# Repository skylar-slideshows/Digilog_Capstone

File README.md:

# Digitally Controlled Analog Mixing Console

### Capstone, 2026, Northeastern University Department of Electrical Engineering

### Contributors: Skylar Denno, Darya Petrova, Evan Forcucci, Xinhao Chen, Luke Garrity, Daniel Salas

### Advisor: [Milad Siami](https://coe.northeastern.edu/people/siami-milad/)

## [Firmware Documentation](https://docs.skylar.lgbt/)

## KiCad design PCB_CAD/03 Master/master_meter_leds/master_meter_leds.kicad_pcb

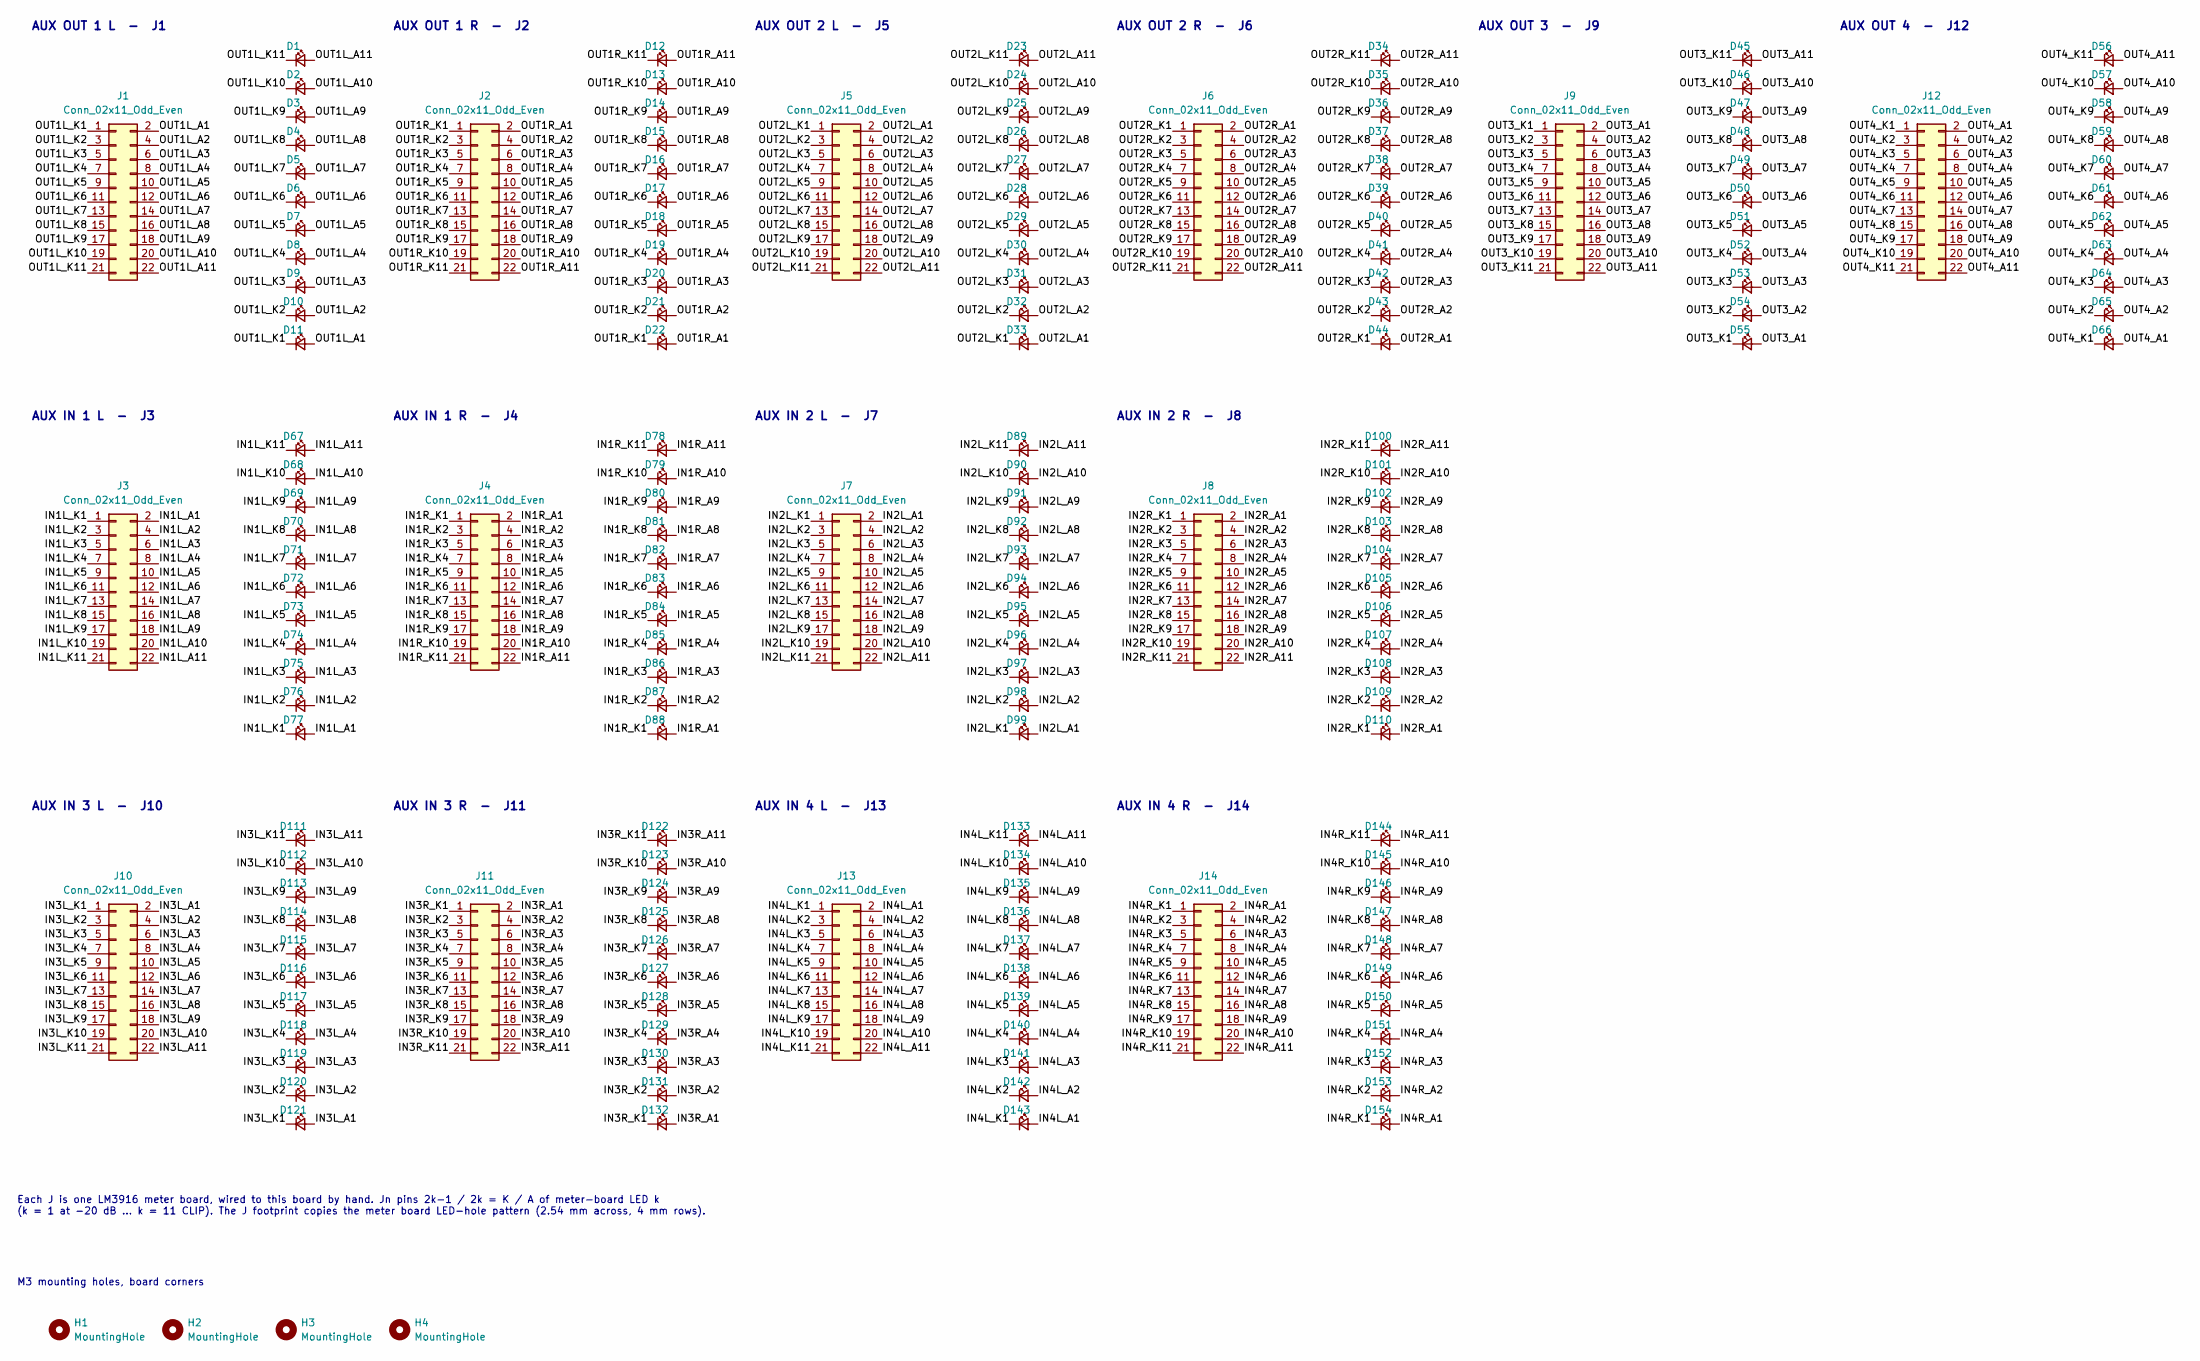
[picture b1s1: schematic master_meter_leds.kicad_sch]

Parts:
D1, D2, D3, D4, D5, D6, D7, D8, D9, D10, D11, D12, D13, D14, D15, D16, D17, D18, D19, D20, D21, D22, D23, D24, D25, D26, D27, D28, D29, D30, D31, D32, D33, D34, D35, D36, D37, D38, D39, D40, D41, D42, D43, D44, D45, D46, D47, D48, D49, D50, D51, D52, D53, D54, D55, D56, D57, D58, D59, D60, D61, D62, D63, D64, D65, D66, D67, D68, D69, D70, D71, D72, D73, D74, D75, D76, D77, D78, D79, D80, D81, D82, D83, D84, D85, D86, D87, D88, D89, D90, D91, D92, D93, D94, D95, D96, D97, D98, D99, D100, D101, D102, D103, D104, D105, D106, D107, D108, D109, D110, D111, D112, D113, D114, D115, D116, D117, D118, D119, D120, D121, D122, D123, D124, D125, D126, D127, D128, D129, D130, D131, D132, D133, D134, D135, D136, D137, D138, D139, D140, D141, D142, D143, D144, D145, D146, D147, D148, D149, D150, D151, D152, D153, D154: LED_Small; LED_Rectangular_W5.0mm_H2.0mm
H1, H2, H3, H4: MountingHole; MountingHole_3.2mm_M3
J1, J2, J3, J4, J5, J6, J7, J8, J9, J10, J11, J12, J13, J14: Conn_02x11_Odd_Even; LED_Meter_Wiring_11x2

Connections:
/IN1L_A1: D77.2 (A), J3.2
/IN1L_A2: D76.2 (A), J3.4
/IN1L_A3: D75.2 (A), J3.6
/IN1L_A4: D74.2 (A), J3.8
/IN1L_A5: D73.2 (A), J3.10
/IN1L_A6: D72.2 (A), J3.12
/IN1L_A7: D71.2 (A), J3.14
/IN1L_A8: D70.2 (A), J3.16
/IN1L_A9: D69.2 (A), J3.18
/IN1L_A10: D68.2 (A), J3.20
/IN1L_A11: D67.2 (A), J3.22
/IN1L_K1: D77.1 (K), J3.1
/IN1L_K2: D76.1 (K), J3.3
/IN1L_K3: D75.1 (K), J3.5
/IN1L_K4: D74.1 (K), J3.7
/IN1L_K5: D73.1 (K), J3.9
/IN1L_K6: D72.1 (K), J3.11
/IN1L_K7: D71.1 (K), J3.13
/IN1L_K8: D70.1 (K), J3.15
/IN1L_K9: D69.1 (K), J3.17
/IN1L_K10: D68.1 (K), J3.19
/IN1L_K11: D67.1 (K), J3.21
/IN1R_A1: D88.2 (A), J4.2
/IN1R_A2: D87.2 (A), J4.4
/IN1R_A3: D86.2 (A), J4.6
/IN1R_A4: D85.2 (A), J4.8
/IN1R_A5: D84.2 (A), J4.10
/IN1R_A6: D83.2 (A), J4.12
/IN1R_A7: D82.2 (A), J4.14
/IN1R_A8: D81.2 (A), J4.16
/IN1R_A9: D80.2 (A), J4.18
/IN1R_A10: D79.2 (A), J4.20
/IN1R_A11: D78.2 (A), J4.22
/IN1R_K1: D88.1 (K), J4.1
/IN1R_K2: D87.1 (K), J4.3
/IN1R_K3: D86.1 (K), J4.5
/IN1R_K4: D85.1 (K), J4.7
/IN1R_K5: D84.1 (K), J4.9
/IN1R_K6: D83.1 (K), J4.11
/IN1R_K7: D82.1 (K), J4.13
/IN1R_K8: D81.1 (K), J4.15
/IN1R_K9: D80.1 (K), J4.17
/IN1R_K10: D79.1 (K), J4.19
/IN1R_K11: D78.1 (K), J4.21
/IN2L_A1: D99.2 (A), J7.2
/IN2L_A2: D98.2 (A), J7.4
/IN2L_A3: D97.2 (A), J7.6
/IN2L_A4: D96.2 (A), J7.8
/IN2L_A5: D95.2 (A), J7.10
/IN2L_A6: D94.2 (A), J7.12
/IN2L_A7: D93.2 (A), J7.14
/IN2L_A8: D92.2 (A), J7.16
/IN2L_A9: D91.2 (A), J7.18
/IN2L_A10: D90.2 (A), J7.20
/IN2L_A11: D89.2 (A), J7.22
/IN2L_K1: D99.1 (K), J7.1
/IN2L_K2: D98.1 (K), J7.3
/IN2L_K3: D97.1 (K), J7.5
/IN2L_K4: D96.1 (K), J7.7
/IN2L_K5: D95.1 (K), J7.9
/IN2L_K6: D94.1 (K), J7.11
/IN2L_K7: D93.1 (K), J7.13
/IN2L_K8: D92.1 (K), J7.15
/IN2L_K9: D91.1 (K), J7.17
/IN2L_K10: D90.1 (K), J7.19
/IN2L_K11: D89.1 (K), J7.21
/IN2R_A1: D110.2 (A), J8.2
/IN2R_A2: D109.2 (A), J8.4
/IN2R_A3: D108.2 (A), J8.6
/IN2R_A4: D107.2 (A), J8.8
/IN2R_A5: D106.2 (A), J8.10
/IN2R_A6: D105.2 (A), J8.12
/IN2R_A7: D104.2 (A), J8.14
/IN2R_A8: D103.2 (A), J8.16
/IN2R_A9: D102.2 (A), J8.18
/IN2R_A10: D101.2 (A), J8.20
/IN2R_A11: D100.2 (A), J8.22
/IN2R_K1: D110.1 (K), J8.1
/IN2R_K2: D109.1 (K), J8.3
/IN2R_K3: D108.1 (K), J8.5
/IN2R_K4: D107.1 (K), J8.7
/IN2R_K5: D106.1 (K), J8.9
/IN2R_K6: D105.1 (K), J8.11
/IN2R_K7: D104.1 (K), J8.13
/IN2R_K8: D103.1 (K), J8.15
/IN2R_K9: D102.1 (K), J8.17
/IN2R_K10: D101.1 (K), J8.19
/IN2R_K11: D100.1 (K), J8.21
/IN3L_A1: D121.2 (A), J10.2
/IN3L_A2: D120.2 (A), J10.4
/IN3L_A3: D119.2 (A), J10.6
/IN3L_A4: D118.2 (A), J10.8
/IN3L_A5: D117.2 (A), J10.10
/IN3L_A6: D116.2 (A), J10.12
/IN3L_A7: D115.2 (A), J10.14
/IN3L_A8: D114.2 (A), J10.16
/IN3L_A9: D113.2 (A), J10.18
/IN3L_A10: D112.2 (A), J10.20
/IN3L_A11: D111.2 (A), J10.22
/IN3L_K1: D121.1 (K), J10.1
/IN3L_K2: D120.1 (K), J10.3
/IN3L_K3: D119.1 (K), J10.5
/IN3L_K4: D118.1 (K), J10.7
/IN3L_K5: D117.1 (K), J10.9
/IN3L_K6: D116.1 (K), J10.11
/IN3L_K7: D115.1 (K), J10.13
/IN3L_K8: D114.1 (K), J10.15
/IN3L_K9: D113.1 (K), J10.17
/IN3L_K10: D112.1 (K), J10.19
/IN3L_K11: D111.1 (K), J10.21
/IN3R_A1: D132.2 (A), J11.2
/IN3R_A2: D131.2 (A), J11.4
/IN3R_A3: D130.2 (A), J11.6
/IN3R_A4: D129.2 (A), J11.8
/IN3R_A5: D128.2 (A), J11.10
/IN3R_A6: D127.2 (A), J11.12
/IN3R_A7: D126.2 (A), J11.14
/IN3R_A8: D125.2 (A), J11.16
/IN3R_A9: D124.2 (A), J11.18
/IN3R_A10: D123.2 (A), J11.20
/IN3R_A11: D122.2 (A), J11.22
/IN3R_K1: D132.1 (K), J11.1
/IN3R_K2: D131.1 (K), J11.3
/IN3R_K3: D130.1 (K), J11.5
/IN3R_K4: D129.1 (K), J11.7
/IN3R_K5: D128.1 (K), J11.9
/IN3R_K6: D127.1 (K), J11.11
/IN3R_K7: D126.1 (K), J11.13
/IN3R_K8: D125.1 (K), J11.15
/IN3R_K9: D124.1 (K), J11.17
/IN3R_K10: D123.1 (K), J11.19
/IN3R_K11: D122.1 (K), J11.21
/IN4L_A1: D143.2 (A), J13.2
/IN4L_A2: D142.2 (A), J13.4
/IN4L_A3: D141.2 (A), J13.6
/IN4L_A4: D140.2 (A), J13.8
/IN4L_A5: D139.2 (A), J13.10
/IN4L_A6: D138.2 (A), J13.12
/IN4L_A7: D137.2 (A), J13.14
/IN4L_A8: D136.2 (A), J13.16
/IN4L_A9: D135.2 (A), J13.18
/IN4L_A10: D134.2 (A), J13.20
/IN4L_A11: D133.2 (A), J13.22
/IN4L_K1: D143.1 (K), J13.1
/IN4L_K2: D142.1 (K), J13.3
/IN4L_K3: D141.1 (K), J13.5
/IN4L_K4: D140.1 (K), J13.7
/IN4L_K5: D139.1 (K), J13.9
/IN4L_K6: D138.1 (K), J13.11
/IN4L_K7: D137.1 (K), J13.13
/IN4L_K8: D136.1 (K), J13.15
/IN4L_K9: D135.1 (K), J13.17
/IN4L_K10: D134.1 (K), J13.19
/IN4L_K11: D133.1 (K), J13.21
/IN4R_A1: D154.2 (A), J14.2
/IN4R_A2: D153.2 (A), J14.4
/IN4R_A3: D152.2 (A), J14.6
/IN4R_A4: D151.2 (A), J14.8
/IN4R_A5: D150.2 (A), J14.10
/IN4R_A6: D149.2 (A), J14.12
/IN4R_A7: D148.2 (A), J14.14
/IN4R_A8: D147.2 (A), J14.16
/IN4R_A9: D146.2 (A), J14.18
/IN4R_A10: D145.2 (A), J14.20
/IN4R_A11: D144.2 (A), J14.22
/IN4R_K1: D154.1 (K), J14.1
/IN4R_K2: D153.1 (K), J14.3
/IN4R_K3: D152.1 (K), J14.5
/IN4R_K4: D151.1 (K), J14.7
/IN4R_K5: D150.1 (K), J14.9
/IN4R_K6: D149.1 (K), J14.11
/IN4R_K7: D148.1 (K), J14.13
/IN4R_K8: D147.1 (K), J14.15
/IN4R_K9: D146.1 (K), J14.17
/IN4R_K10: D145.1 (K), J14.19
/IN4R_K11: D144.1 (K), J14.21
/OUT1L_A1: D11.2 (A), J1.2
/OUT1L_A2: D10.2 (A), J1.4
/OUT1L_A3: D9.2 (A), J1.6
/OUT1L_A4: D8.2 (A), J1.8
/OUT1L_A5: D7.2 (A), J1.10
/OUT1L_A6: D6.2 (A), J1.12
/OUT1L_A7: D5.2 (A), J1.14
/OUT1L_A8: D4.2 (A), J1.16
/OUT1L_A9: D3.2 (A), J1.18
/OUT1L_A10: D2.2 (A), J1.20
/OUT1L_A11: D1.2 (A), J1.22
/OUT1L_K1: D11.1 (K), J1.1
/OUT1L_K2: D10.1 (K), J1.3
/OUT1L_K3: D9.1 (K), J1.5
/OUT1L_K4: D8.1 (K), J1.7
/OUT1L_K5: D7.1 (K), J1.9
/OUT1L_K6: D6.1 (K), J1.11
/OUT1L_K7: D5.1 (K), J1.13
/OUT1L_K8: D4.1 (K), J1.15
/OUT1L_K9: D3.1 (K), J1.17
/OUT1L_K10: D2.1 (K), J1.19
/OUT1L_K11: D1.1 (K), J1.21
/OUT1R_A1: D22.2 (A), J2.2
/OUT1R_A2: D21.2 (A), J2.4
/OUT1R_A3: D20.2 (A), J2.6
/OUT1R_A4: D19.2 (A), J2.8
/OUT1R_A5: D18.2 (A), J2.10
/OUT1R_A6: D17.2 (A), J2.12
/OUT1R_A7: D16.2 (A), J2.14
/OUT1R_A8: D15.2 (A), J2.16
/OUT1R_A9: D14.2 (A), J2.18
/OUT1R_A10: D13.2 (A), J2.20
/OUT1R_A11: D12.2 (A), J2.22
/OUT1R_K1: D22.1 (K), J2.1
/OUT1R_K2: D21.1 (K), J2.3
/OUT1R_K3: D20.1 (K), J2.5
/OUT1R_K4: D19.1 (K), J2.7
/OUT1R_K5: D18.1 (K), J2.9
/OUT1R_K6: D17.1 (K), J2.11
/OUT1R_K7: D16.1 (K), J2.13
/OUT1R_K8: D15.1 (K), J2.15
/OUT1R_K9: D14.1 (K), J2.17
/OUT1R_K10: D13.1 (K), J2.19
/OUT1R_K11: D12.1 (K), J2.21
/OUT2L_A1: D33.2 (A), J5.2
/OUT2L_A2: D32.2 (A), J5.4
/OUT2L_A3: D31.2 (A), J5.6
/OUT2L_A4: D30.2 (A), J5.8
/OUT2L_A5: D29.2 (A), J5.10
/OUT2L_A6: D28.2 (A), J5.12
/OUT2L_A7: D27.2 (A), J5.14
/OUT2L_A8: D26.2 (A), J5.16
/OUT2L_A9: D25.2 (A), J5.18
/OUT2L_A10: D24.2 (A), J5.20
/OUT2L_A11: D23.2 (A), J5.22
/OUT2L_K1: D33.1 (K), J5.1
/OUT2L_K2: D32.1 (K), J5.3
/OUT2L_K3: D31.1 (K), J5.5
/OUT2L_K4: D30.1 (K), J5.7
/OUT2L_K5: D29.1 (K), J5.9
/OUT2L_K6: D28.1 (K), J5.11
/OUT2L_K7: D27.1 (K), J5.13
/OUT2L_K8: D26.1 (K), J5.15
/OUT2L_K9: D25.1 (K), J5.17
/OUT2L_K10: D24.1 (K), J5.19
/OUT2L_K11: D23.1 (K), J5.21
/OUT2R_A1: D44.2 (A), J6.2
/OUT2R_A2: D43.2 (A), J6.4
/OUT2R_A3: D42.2 (A), J6.6
/OUT2R_A4: D41.2 (A), J6.8
/OUT2R_A5: D40.2 (A), J6.10
/OUT2R_A6: D39.2 (A), J6.12
/OUT2R_A7: D38.2 (A), J6.14
/OUT2R_A8: D37.2 (A), J6.16
/OUT2R_A9: D36.2 (A), J6.18
/OUT2R_A10: D35.2 (A), J6.20
/OUT2R_A11: D34.2 (A), J6.22
/OUT2R_K1: D44.1 (K), J6.1
/OUT2R_K2: D43.1 (K), J6.3
/OUT2R_K3: D42.1 (K), J6.5
/OUT2R_K4: D41.1 (K), J6.7
/OUT2R_K5: D40.1 (K), J6.9
/OUT2R_K6: D39.1 (K), J6.11
/OUT2R_K7: D38.1 (K), J6.13
/OUT2R_K8: D37.1 (K), J6.15
/OUT2R_K9: D36.1 (K), J6.17
/OUT2R_K10: D35.1 (K), J6.19
/OUT2R_K11: D34.1 (K), J6.21
/OUT3_A1: D55.2 (A), J9.2
/OUT3_A2: D54.2 (A), J9.4
/OUT3_A3: D53.2 (A), J9.6
/OUT3_A4: D52.2 (A), J9.8
/OUT3_A5: D51.2 (A), J9.10
/OUT3_A6: D50.2 (A), J9.12
/OUT3_A7: D49.2 (A), J9.14
/OUT3_A8: D48.2 (A), J9.16
/OUT3_A9: D47.2 (A), J9.18
/OUT3_A10: D46.2 (A), J9.20
/OUT3_A11: D45.2 (A), J9.22
/OUT3_K1: D55.1 (K), J9.1
/OUT3_K2: D54.1 (K), J9.3
/OUT3_K3: D53.1 (K), J9.5
/OUT3_K4: D52.1 (K), J9.7
/OUT3_K5: D51.1 (K), J9.9
/OUT3_K6: D50.1 (K), J9.11
/OUT3_K7: D49.1 (K), J9.13
/OUT3_K8: D48.1 (K), J9.15
/OUT3_K9: D47.1 (K), J9.17
/OUT3_K10: D46.1 (K), J9.19
/OUT3_K11: D45.1 (K), J9.21
/OUT4_A1: D66.2 (A), J12.2
/OUT4_A2: D65.2 (A), J12.4
/OUT4_A3: D64.2 (A), J12.6
/OUT4_A4: D63.2 (A), J12.8
/OUT4_A5: D62.2 (A), J12.10
/OUT4_A6: D61.2 (A), J12.12
/OUT4_A7: D60.2 (A), J12.14
/OUT4_A8: D59.2 (A), J12.16
/OUT4_A9: D58.2 (A), J12.18
/OUT4_A10: D57.2 (A), J12.20
/OUT4_A11: D56.2 (A), J12.22
/OUT4_K1: D66.1 (K), J12.1
/OUT4_K2: D65.1 (K), J12.3
/OUT4_K3: D64.1 (K), J12.5
/OUT4_K4: D63.1 (K), J12.7
/OUT4_K5: D62.1 (K), J12.9
/OUT4_K6: D61.1 (K), J12.11
/OUT4_K7: D60.1 (K), J12.13
/OUT4_K8: D59.1 (K), J12.15
/OUT4_K9: D58.1 (K), J12.17
/OUT4_K10: D57.1 (K), J12.19
/OUT4_K11: D56.1 (K), J12.21

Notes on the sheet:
AUX IN 2 R - J8
AUX OUT 1 R - J2
AUX OUT 2 R - J6
AUX IN 3 L - J10
AUX OUT 3 - J9
AUX IN 4 L - J13
M3 mounting holes, board corners
Each J is one LM3916 meter board, wired to this board by hand. Jn pins 2k-1 / 2k = K / A of meter-board LED k (k = 1 at -20 dB ... k = 11 CLIP). The J footprint copies the meter board LED-hole pattern (2.54 mm across, 4 mm rows).
AUX OUT 1 L - J1
AUX IN 2 L - J7
AUX OUT 4 - J12
AUX IN 1 L - J3
AUX IN 3 R - J11
AUX IN 4 R - J14
AUX OUT 2 L - J5
AUX IN 1 R - J4

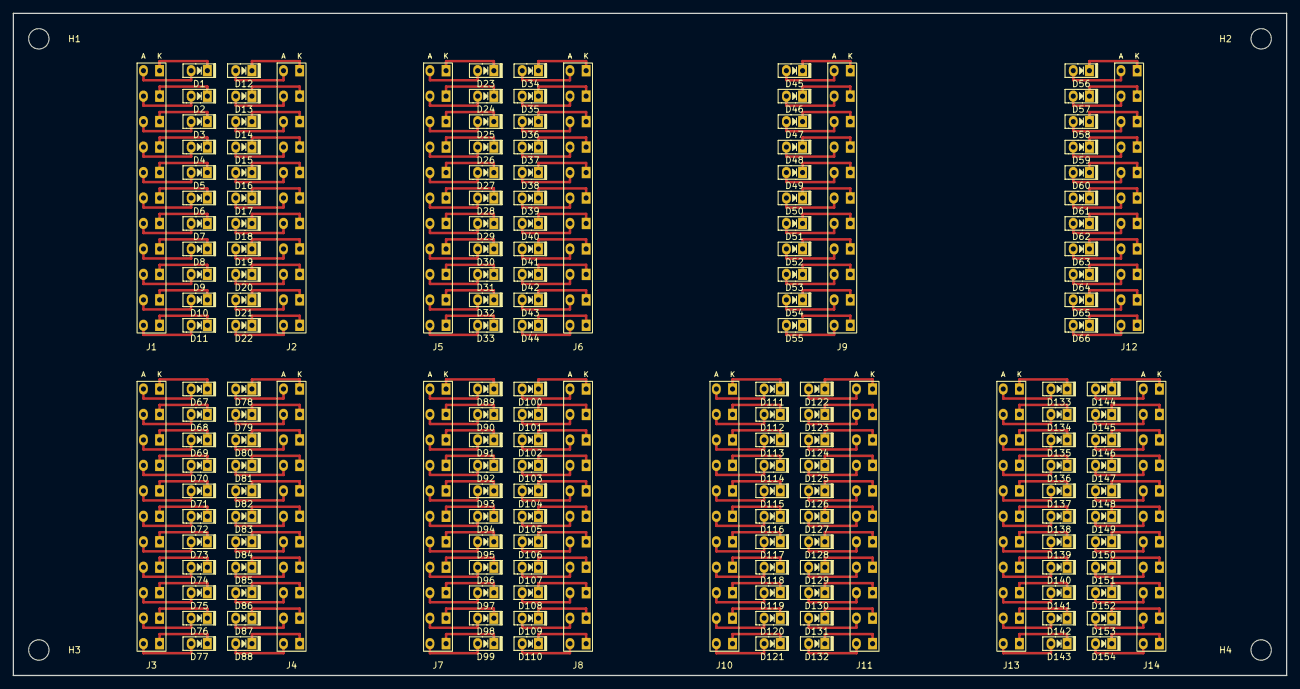
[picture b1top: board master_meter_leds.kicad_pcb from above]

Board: 2 copper layers, 200.0 x 104.0 mm, 172 parts (0 on the bottom side), 308 nets.

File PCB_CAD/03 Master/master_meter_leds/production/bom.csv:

Designator,Footprint,Quantity,Value,LCSC Part #
"D1, D10, D100, D101, D102, D103, D104, D105, D106, D107, D108, D109, D11, D110, D111, D112, D113, D114, D115, D116, D117, D118, D119, D12, D120, D121, D122, D123, D124, D125, D126, D127, D128, D129, D13, D130, D131, D132, D133, D134, D135, D136, D137, D138, D139, D14, D140, D141, D142, D143, D144, D145, D146, D147, D148, D149, D15, D150, D151, D152, D153, D154, D16, D17, D18, D19, D2, D20, D21, D22, D23, D24, D25, D26, D27, D28, D29, D3, D30, D31, D32, D33, D34, D35, D36, D37, D38, D39, D4, D40, D41, D42, D43, D44, D45, D46, D47, D48, D49, D5, D50, D51, D52, D53, D54, D55, D56, D57, D58, D59, D6, D60, D61, D62, D63, D64, D65, D66, D67, D68, D69, D7, D70, D71, D72, D73, D74, D75, D76, D77, D78, D79, D8, D80, D81, D82, D83, D84, D85, D86, D87, D88, D89, D9, D90, D91, D92, D93, D94, D95, D96, D97, D98, D99",LED_Rectangular_W5.0mm_H2.0mm,154,LED_Small,
"J1, J10, J11, J12, J13, J14, J2, J3, J4, J5, J6, J7, J8, J9",LED_Meter_Wiring_11x2,14,Conn_02x11_Odd_Even,
